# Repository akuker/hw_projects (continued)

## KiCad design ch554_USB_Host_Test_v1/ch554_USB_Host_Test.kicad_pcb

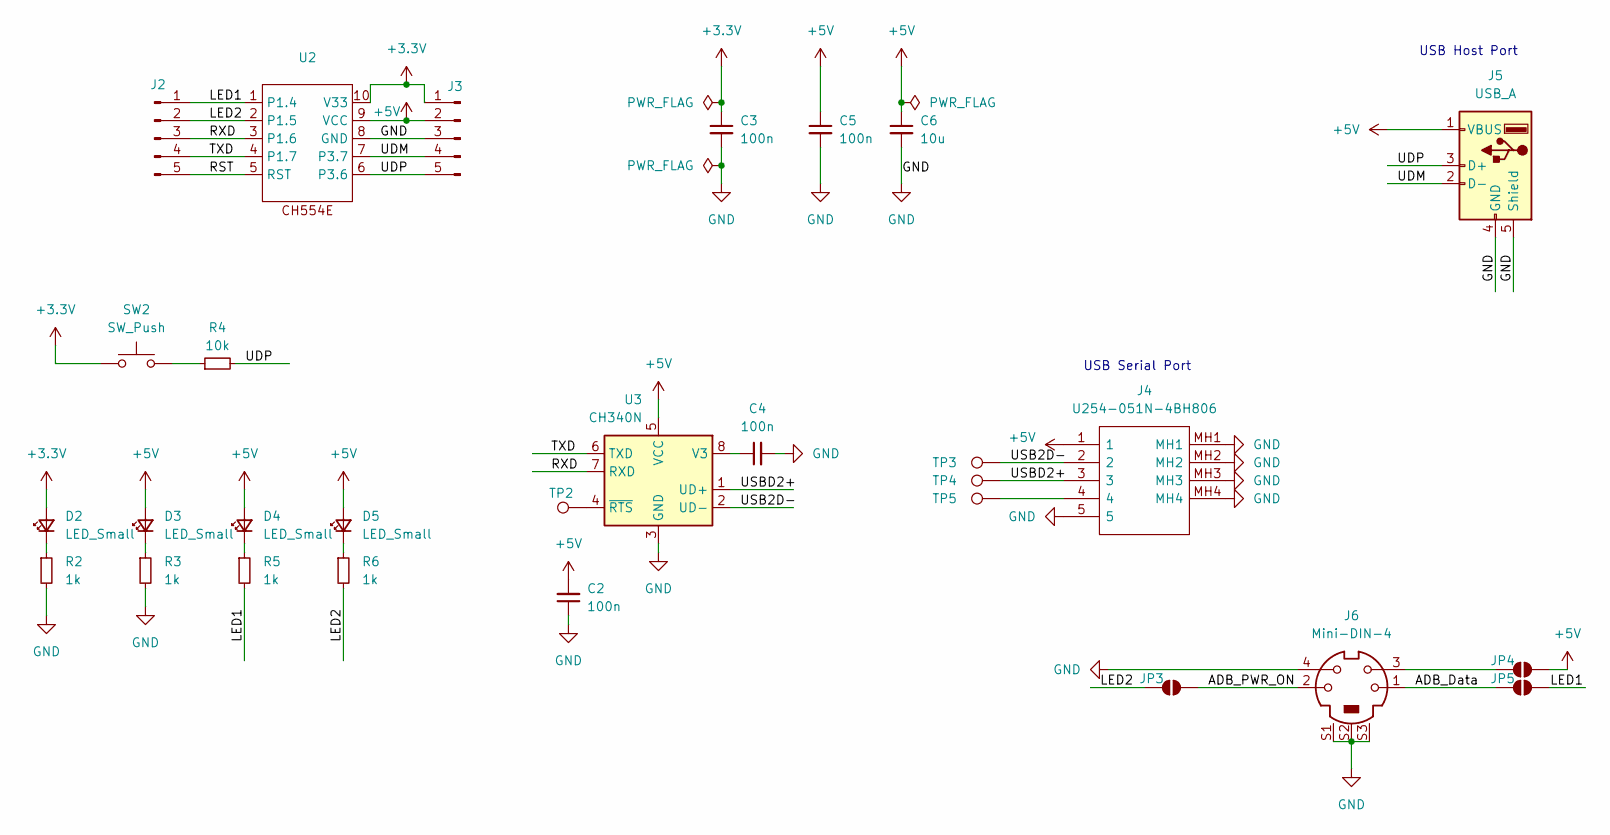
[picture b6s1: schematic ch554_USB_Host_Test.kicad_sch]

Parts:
C2, C3, C4, C5: 100n; C_0805_2012Metric_Pad1.18x1.45mm_HandSolder; LCSC C49678
C6: 10u; C_0603_1608Metric_Pad1.08x0.95mm_HandSolder; LCSC C2909630
D2, D3, D4, D5: LED_Small; LED_0603_1608Metric_Pad1.05x0.95mm_HandSolder; LCSC C2286
J2, J3: Conn_01x05_Pin; PinHeader_1x05_P2.54mm_Vertical
J4: U254-051N-4BH806; U254051N4BH806; Manufacturer_Part_Number U254-051N-4BH806; LCSC C319170
J5: USB_A; USB_A_Molex_67643_Horizontal; LCSC C2346
J6: Mini-DIN-4; CUI_MD2-40ST-SMT
JP3, JP4, JP5: SolderJumper_2_Open; SolderJumper-2_P1.3mm_Open_RoundedPad1.0x1.5mm
R2, R3, R5, R6: 1k; R_0805_2012Metric_Pad1.20x1.40mm_HandSolder; LCSC C17513
R4: 10k; R_0805_2012Metric_Pad1.20x1.40mm_HandSolder; LCSC C17414
SW2: SW_Push; SW_Push_1P1T_XKB_TS-1187A; LCSC C318884
TP2, TP3, TP4, TP5: TestPoint; TestPoint_Pad_D1.0mm
U2: MSOP-10_3x3mm_P0.5mm; LCSC C111293
U3: CH340N; SOP-8_3.9x4.9mm_P1.27mm; LCSC C2977777

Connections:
+3.3V: C3.1, D2.2 (A), J3.1, SW2.1, U2.10 (V33)
+5V: C2.2, C5.1, C6.1, D3.2 (A), D4.2 (A), D5.2 (A), J3.2, J4.1, J5.1 (VBUS), JP4.2 (B), U2.9 (VCC), U3.5 (VCC)
/ADB_Data: J6.1, JP5.1 (A)
/ADB_PWR_ON: J6.2, JP3.2 (B)
/LED1: J2.1, JP5.2 (B), R5.2, U2.1 (P1.4)
/LED2: J2.2, JP3.1 (A), R6.2, U2.2 (P1.5)
/RST: J2.5, U2.5 (RST)
/RXD: J2.3, U2.3 (P1.6), U3.7 (RXD)
/TXD: J2.4, U2.4 (P1.7), U3.6 (TXD)
/UDM: J3.4, J5.2 (D-), U2.7 (P3.7)
/UDP: J3.5, J5.3 (D+), R4.2, U2.6 (P3.6)
/USB2D-: J4.2, TP3.1, U3.2 (UD-)
/USBD2+: J4.3, TP4.1, U3.1 (UD+)
GND: C2.1, C3.2, C4.2, C5.2, C6.2, J3.3, J4.5, J4.MH1, J4.MH2, J4.MH3, J4.MH4, J5.4 (GND), J5.5 (Shield), J6.4, J6.S1, J6.S2, J6.S3, R2.2, R3.2, U2.8 (GND), U3.3 (GND)
unnamed: D2.1 (K), R2.1
unnamed: D3.1 (K), R3.1
unnamed: D4.1 (K), R5.1
unnamed: D5.1 (K), R6.1
unnamed: J4.4, TP5.1
unnamed: J6.3, JP4.1 (A)
unnamed: R4.1, SW2.2
unnamed: C4.1, U3.8 (V3)
unnamed: TP2.1, U3.4 (~RTS)

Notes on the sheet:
USB Host Port
USB Serial Port

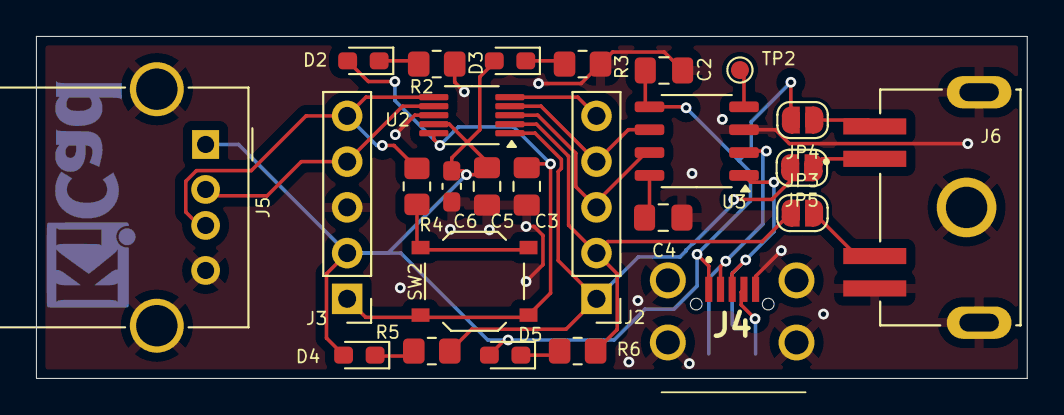
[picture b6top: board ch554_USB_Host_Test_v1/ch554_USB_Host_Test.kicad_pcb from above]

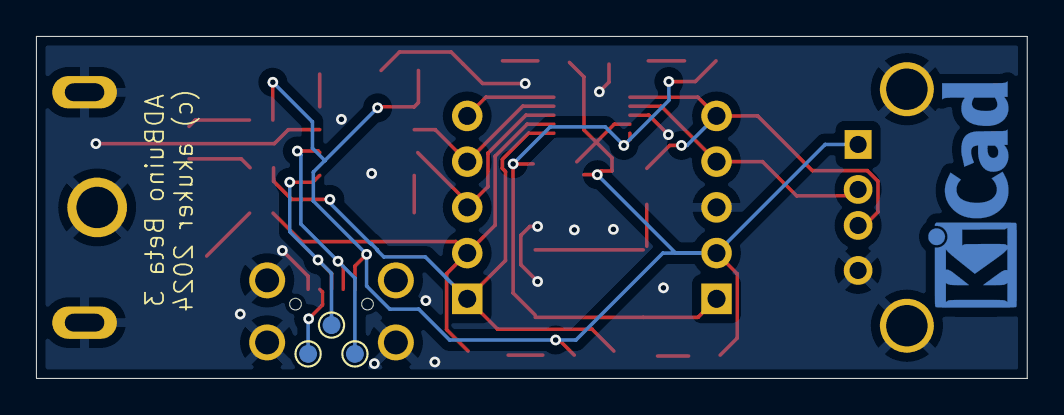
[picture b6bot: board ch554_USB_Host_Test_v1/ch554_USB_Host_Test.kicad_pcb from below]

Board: 2 copper layers, 55.0 x 19.0 mm, 29 parts (3 on the bottom side), 23 nets.

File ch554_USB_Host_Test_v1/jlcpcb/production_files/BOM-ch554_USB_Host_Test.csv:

Comment,Designator,Footprint,LCSC
~,U2,MSOP-10_3x3mm_P0.5mm,C111293
10k,R4,R_0805_2012Metric_Pad1.20x1.40mm_HandSolder,C17414
1k,"R2,R3,R5,R6",R_0805_2012Metric_Pad1.20x1.40mm_HandSolder,C17513
LED_Small,"D2,D3,D4,D5",LED_0603_1608Metric_Pad1.05x0.95mm_HandSolder,C2286
USB_A,J5,USB_A_Molex_67643_Horizontal,C2346
10u,C6,C_0603_1608Metric_Pad1.08x0.95mm_HandSolder,C2909630
CH340N,U3,SOP-8_3.9x4.9mm_P1.27mm,C2977777
SW_Push,SW2,SW_Push_1P1T_XKB_TS-1187A,C318884
U254-051N-4BH806,J4,U254051N4BH806,C319170
100n,"C2,C3,C4,C5",C_0805_2012Metric_Pad1.18x1.45mm_HandSolder,C49678

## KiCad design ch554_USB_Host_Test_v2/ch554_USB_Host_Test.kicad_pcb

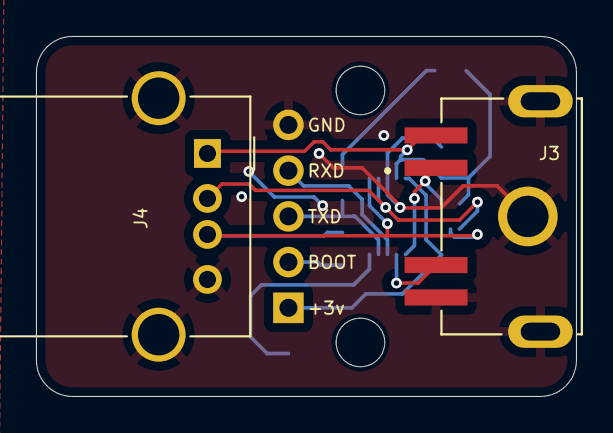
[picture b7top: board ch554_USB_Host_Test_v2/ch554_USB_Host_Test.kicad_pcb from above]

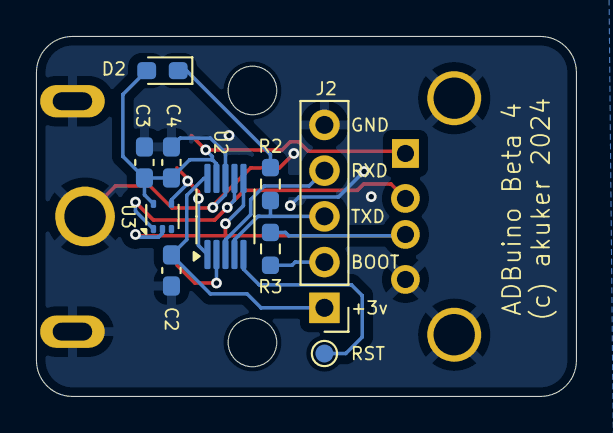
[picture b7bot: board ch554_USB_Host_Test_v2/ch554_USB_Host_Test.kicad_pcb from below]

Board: 2 copper layers, 30.0 x 20.0 mm, 14 parts (10 on the bottom side), 12 nets.

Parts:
C2, C3: 100n; C_0603_1608Metric_Pad1.08x0.95mm_HandSolder
C4: 10u; C_0603_1608Metric_Pad1.08x0.95mm_HandSolder
D2: LED_Small; LED_0603_1608Metric_Pad1.05x0.95mm_HandSolder
H2, H3: MountingHole; MountingHole_2.7mm_M2.5
J2: Conn_01x03_Pin; PinHeader_1x05_P2.54mm_Vertical
J3: Mini-DIN-4; CUI_MD2-40ST-SMT
J4: USB_A; USB_A_Molex_67643_Horizontal
R2, R3: 10k; R_0603_1608Metric_Pad0.98x0.95mm_HandSolder
TP2: TestPoint_Small; TestPoint_Pad_D1.0mm
U2: MSOP-10_3x3mm_P0.5mm
U3: TPD3E001DRLR; SOT-553

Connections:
+3.3V: C2.1, J2.1, U2.10 (V33)
+5V: C3.1, C4.1, D2.2 (A), J3.3, J4.1 (VBUS), U2.9 (VCC), U3.5
/ADB_Data: J3.1, U2.1 (P1.4), U3.4 (IO3)
/ADB_PWR_ON: J3.2, U2.2 (P1.5)
/RST: TP2.1, U2.5 (RST)
/RXD: J2.4, U2.3 (P1.6)
/TXD: J2.3, R2.2, U2.4 (P1.7)
/UDM: J4.2 (D-), U2.7 (P3.7), U3.1 (IO1)
/UDP: J4.3 (D+), R3.2, U2.6 (P3.6), U3.2 (IO2)
GND: C2.2, C3.2, C4.2, J2.5, J3.4, J3.S1, J3.S2, J3.S3, J4.4 (GND), J4.5 (Shield), U2.8 (GND), U3.3
unnamed: D2.1 (K), R2.1
unnamed: J2.2, R3.1

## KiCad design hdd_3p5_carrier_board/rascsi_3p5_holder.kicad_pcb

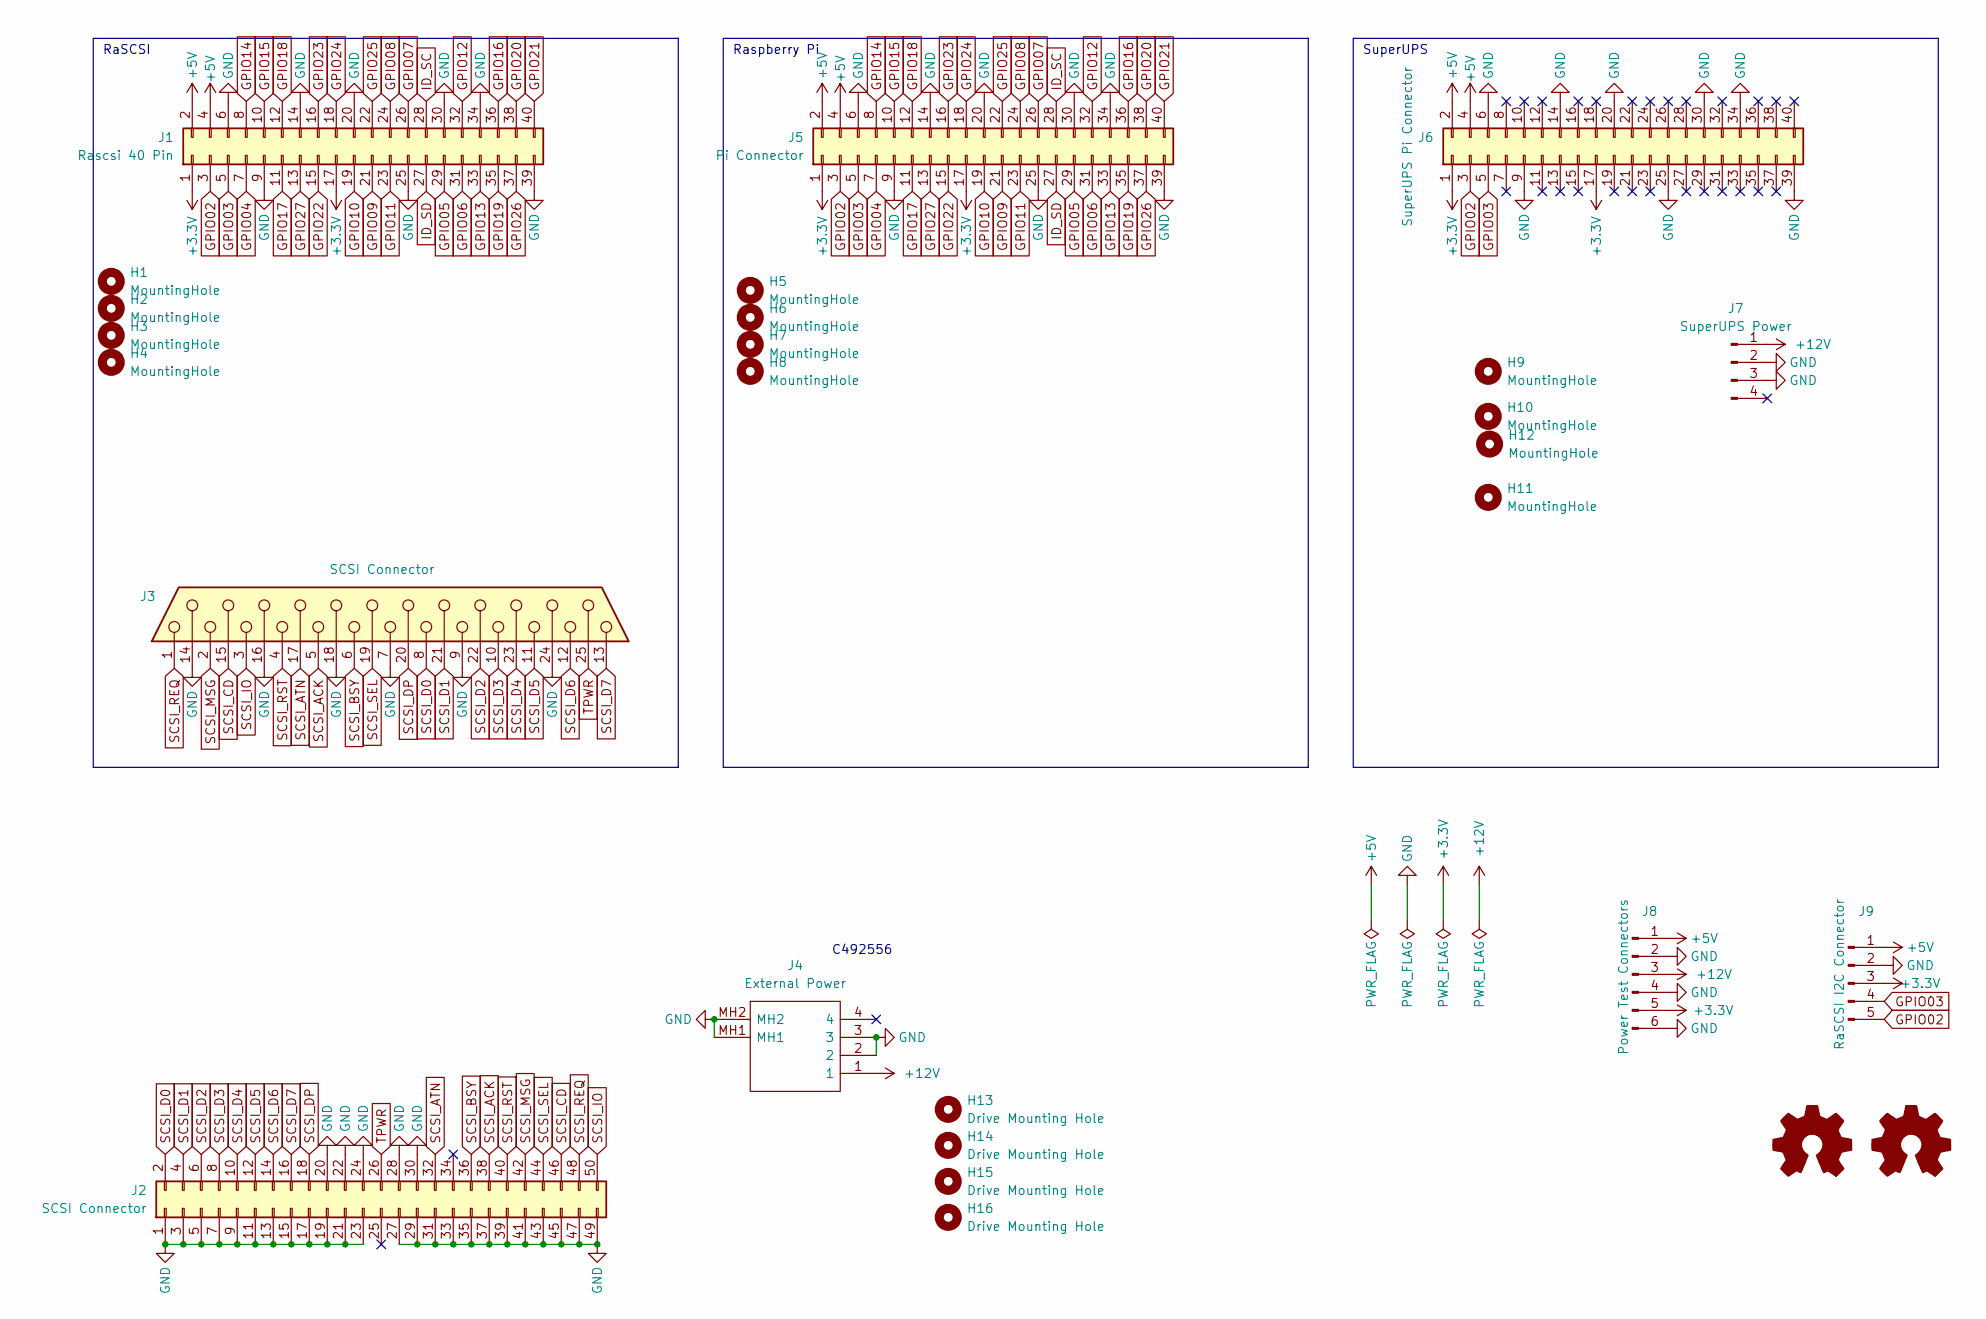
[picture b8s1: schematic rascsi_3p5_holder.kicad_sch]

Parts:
H1, H2, H3, H4, H5, H6, H7, H8, H9, H10, H11, H12: MountingHole; MountingHole_2.7mm_M2.5
H13, H14, H15, H16: Drive Mounting Hole; MountingHole_3.2mm_M3
J1: Rascsi 40 Pin; PinHeader_2x20_P2.54mm_Vertical
J2: SCSI Connector; PinHeader_2x25_P2.54mm_Horizontal
J3: SCSI Connector; DSUB-25_Female_Vertical_P2.77x2.84mm
J4: External Power; 1748041; Mouser Part Number 571-1748041
J5: Pi Connector; PinHeader_2x20_P2.54mm_Vertical
J6: SuperUPS Pi Connector; PinHeader_2x20_P2.54mm_Vertical
J7: SuperUPS Power; PinHeader_1x04_P2.54mm_Vertical
J8: Power Test Connectors; PinHeader_1x06_P2.54mm_Vertical
J9: RaSCSI I2C Connector; PinHeader_1x05_P2.54mm_Vertical

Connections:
+3V3: J1.1, J1.17, J5.1, J5.17, J6.1, J6.17, J8.5, J9.3
+5V: J1.2, J1.4, J5.2, J5.4, J6.2, J6.4, J8.1, J9.1
+12V: J4.1, J7.1, J8.3
GND: J1.6, J1.9, J1.14, J1.20, J1.25, J1.30, J1.34, J1.39, J2.1, J2.3, J2.5, J2.7, J2.9, J2.11, J2.13, J2.15, J2.17, J2.19, J2.20, J2.21, J2.22, J2.23, J2.24, J2.27, J2.28, J2.29, J2.30, J2.31, J2.33, J2.35, J2.37, J2.39, J2.41, J2.43, J2.45, J2.47, J2.49, J3.7, J3.9, J3.14, J3.16, J3.18, J3.24, J4.2, J4.3, J4.MH1, J4.MH2, J5.6, J5.9, J5.14, J5.20, J5.25, J5.30, J5.34, J5.39, J6.6, J6.9, J6.14, J6.20, J6.25, J6.30, J6.34, J6.39, J7.2, J7.3, J8.2, J8.4, J8.6, J9.2
GPIO02: J1.3, J5.3, J6.3, J9.5
GPIO03: J1.5, J5.5, J6.5, J9.4
GPIO04: J1.7, J5.7
GPIO05: J1.29, J5.29
GPIO06: J1.31, J5.31
GPIO07: J1.26, J5.26
GPIO08: J1.24, J5.24
GPIO09: J1.21, J5.21
GPIO10: J1.19, J5.19
GPIO11: J1.23, J5.23
GPIO12: J1.32, J5.32
GPIO13: J1.33, J5.33
GPIO14: J1.8, J5.8
GPIO15: J1.10, J5.10
GPIO16: J1.36, J5.36
GPIO17: J1.11, J5.11
GPIO18: J1.12, J5.12
GPIO19: J1.35, J5.35
GPIO20: J1.38, J5.38
GPIO21: J1.40, J5.40
GPIO22: J1.15, J5.15
GPIO23: J1.16, J5.16
GPIO24: J1.18, J5.18
GPIO25: J1.22, J5.22
GPIO26: J1.37, J5.37
GPIO27: J1.13, J5.13
ID_SC: J1.28, J5.28
ID_SD: J1.27, J5.27
SCSI_ACK: J2.38, J3.5
SCSI_ATN: J2.32, J3.17
SCSI_BSY: J2.36, J3.6
SCSI_CD: J2.46, J3.15
SCSI_D0: J2.2, J3.8
SCSI_D1: J2.4, J3.21
SCSI_D2: J2.6, J3.22
SCSI_D3: J2.8, J3.10
SCSI_D4: J2.10, J3.23
SCSI_D5: J2.12, J3.11
SCSI_D6: J2.14, J3.12
SCSI_D7: J2.16, J3.13
SCSI_DP: J2.18, J3.20
SCSI_IO: J2.50, J3.3
SCSI_MSG: J2.42, J3.2
SCSI_REQ: J2.48, J3.1
SCSI_RST: J2.40, J3.4
SCSI_SEL: J2.44, J3.19
TPWR: J2.26, J3.25

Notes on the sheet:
C492556
RaSCSI
SuperUPS
Raspberry Pi

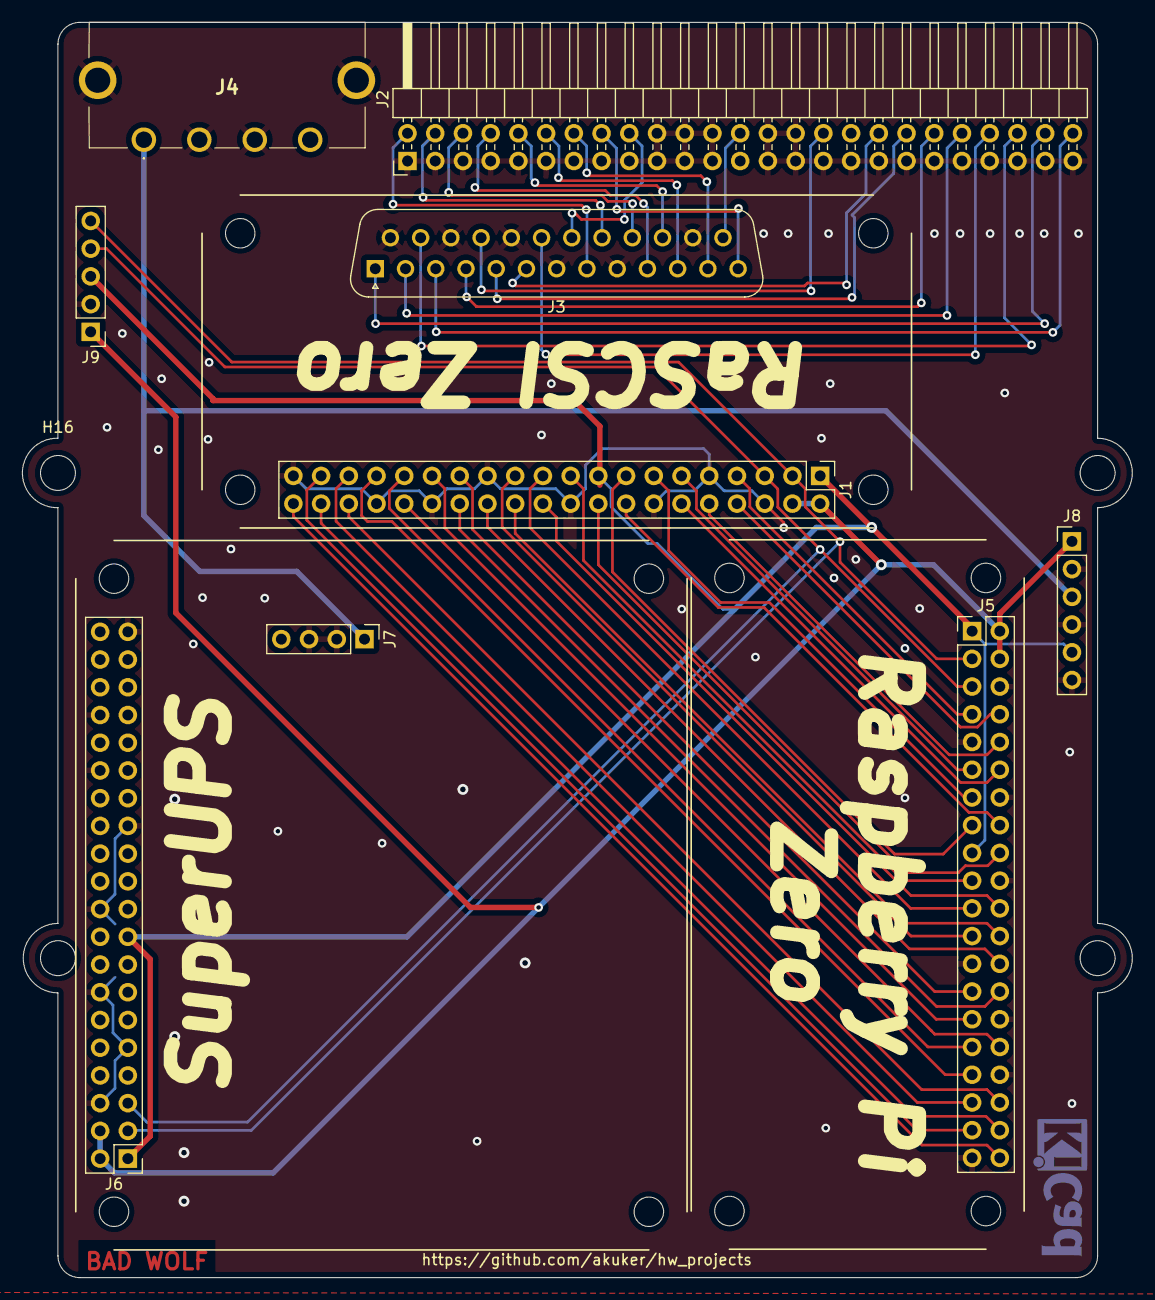
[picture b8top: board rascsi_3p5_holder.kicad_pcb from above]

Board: 2 copper layers, 101.7 x 115.0 mm, 25 parts (0 on the bottom side), 51 nets.
